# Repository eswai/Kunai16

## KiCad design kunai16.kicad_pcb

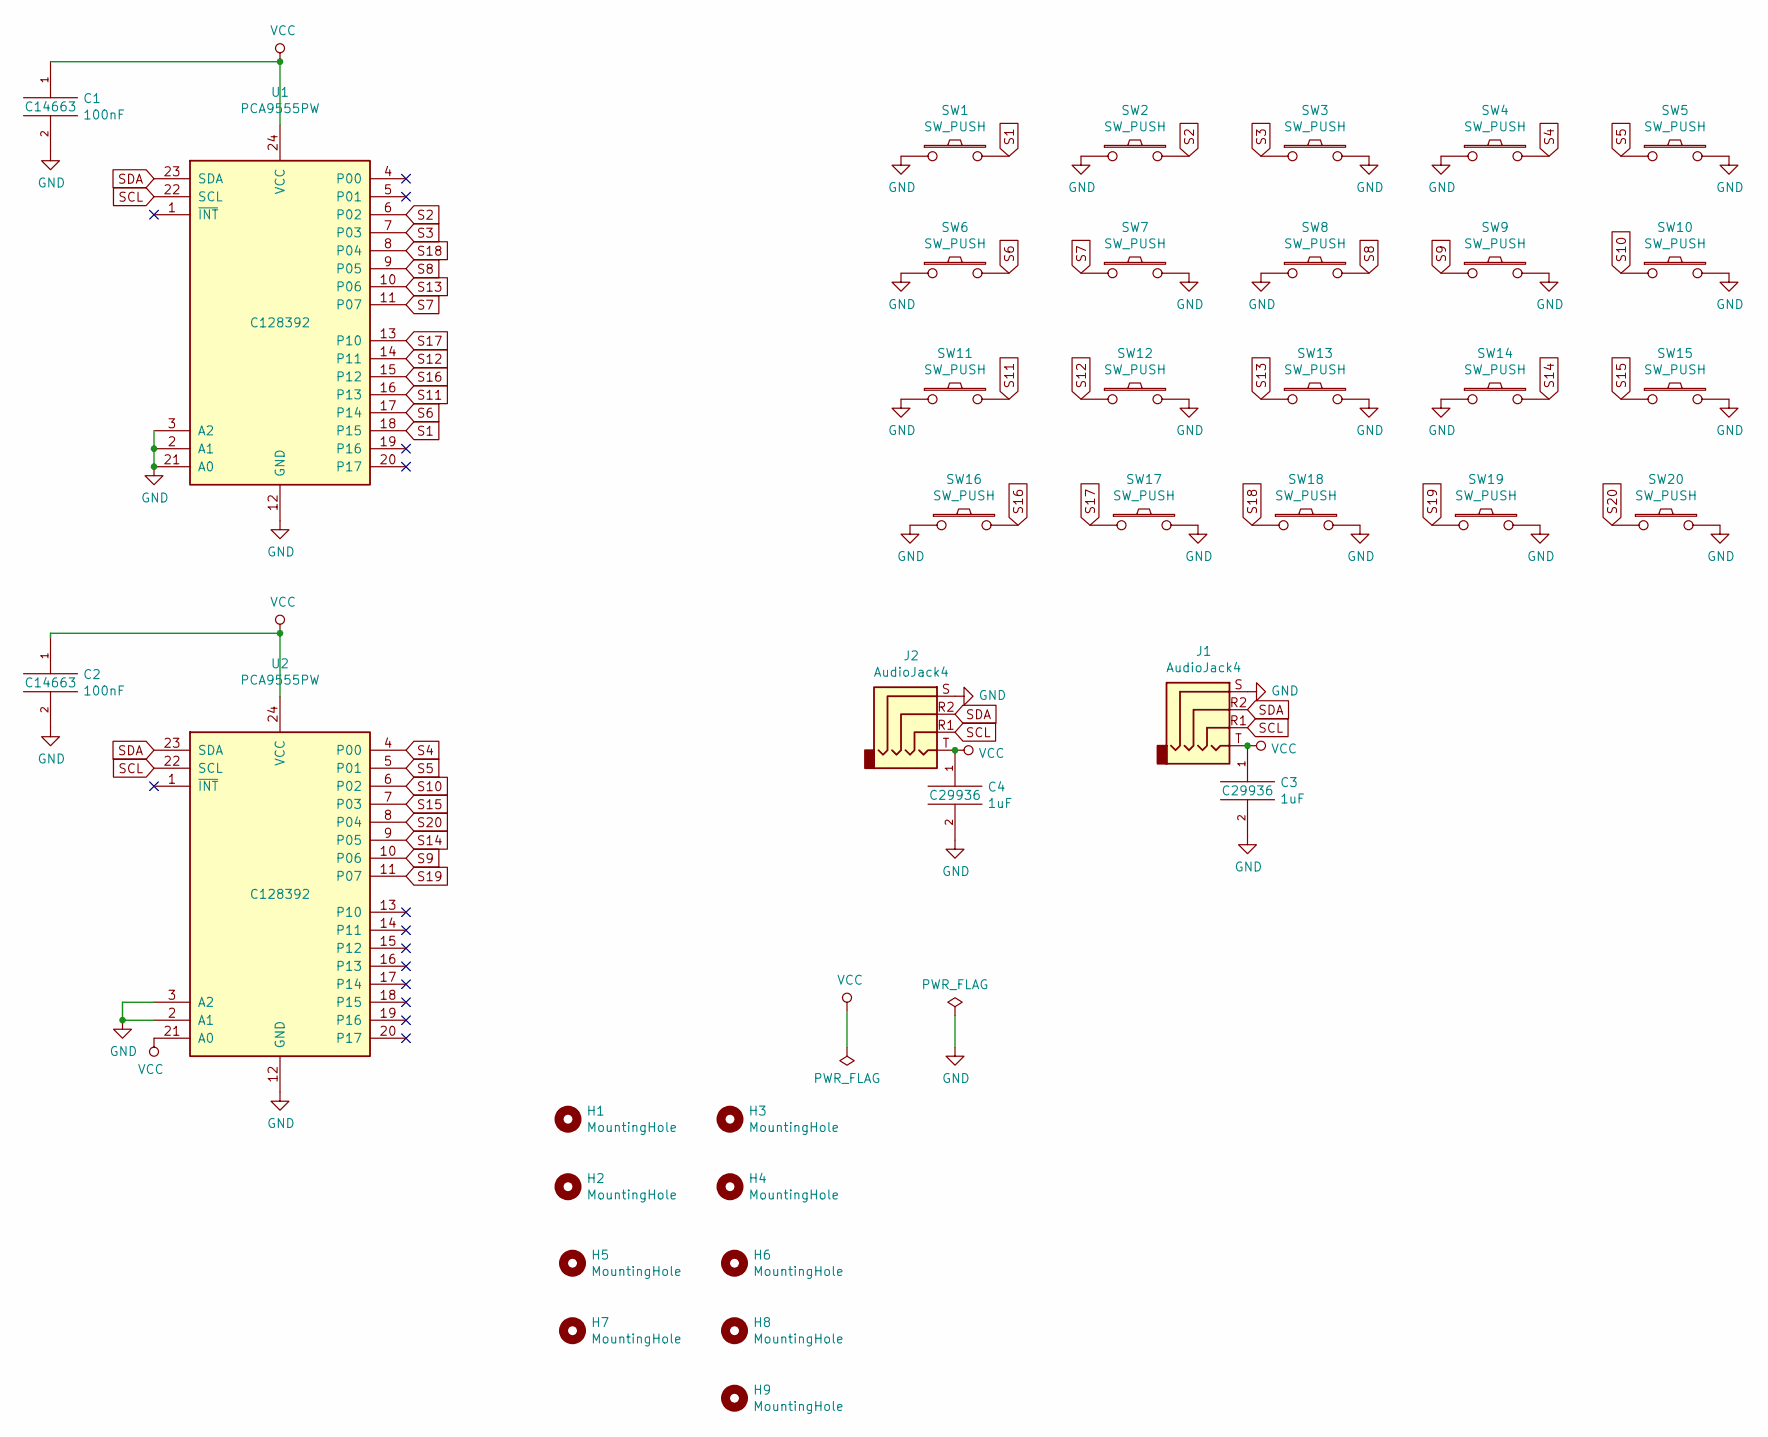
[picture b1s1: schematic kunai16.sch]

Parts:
C1, C2: 100nF; C_0603_1608Metric_Pad1.05x0.95mm_HandSolder; LCSC C14663
C3, C4: 1uF; C_0603_1608Metric_Pad1.05x0.95mm_HandSolder; LCSC C29936
H1, H2, H3, H4, H5, H6, H7, H8, H9: MountingHole; MountingHole_2.2mm_M2
J1, J2: AudioJack4; MJ-4PP-9_v3
SW1, SW2, SW3, SW4, SW5, SW6, SW7, SW8, SW9, SW10, SW11, SW12, SW13, SW14, SW15, SW16, SW17, SW18, SW19, SW20: SW_PUSH; CherryMX_Hotswap
U1, U2: PCA9555PW; TSSOP-24_4.4x7.8mm_P0.65mm; LCSC C128392

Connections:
GND: C1.2, C2.2, C3.2, C4.2, J1.S, J2.S, SW1.1, SW2.1, SW3.2, SW4.1, SW5.2, SW6.1, SW7.2, SW8.1, SW9.2, SW10.2, SW11.1, SW12.2, SW13.2, SW14.1, SW15.2, SW16.1, SW17.2, SW18.2, SW19.2, SW20.2, U1.2 (A1), U1.3 (A2), U1.12 (GND), U1.21 (A0), U2.2 (A1), U2.3 (A2), U2.12 (GND)
S1: SW1.2, U1.18 (P15)
S2: SW2.2, U1.6 (P02)
S3: SW3.1, U1.7 (P03)
S4: SW4.2, U2.4 (P00)
S5: SW5.1, U2.5 (P01)
S6: SW6.2, U1.17 (P14)
S7: SW7.1, U1.11 (P07)
S8: SW8.2, U1.9 (P05)
S9: SW9.1, U2.10 (P06)
S10: SW10.1, U2.6 (P02)
S11: SW11.2, U1.16 (P13)
S12: SW12.1, U1.14 (P11)
S13: SW13.1, U1.10 (P06)
S14: SW14.2, U2.9 (P05)
S15: SW15.1, U2.7 (P03)
S16: SW16.2, U1.15 (P12)
S17: SW17.1, U1.13 (P10)
S18: SW18.1, U1.8 (P04)
S19: SW19.1, U2.11 (P07)
S20: SW20.1, U2.8 (P04)
SCL: J1.R1, J2.R1, U1.22 (SCL), U2.22 (SCL)
SDA: J1.R2, J2.R2, U1.23 (SDA), U2.23 (SDA)
VCC: C1.1, C2.1, C3.1, C4.1, J1.T, J2.T, U1.24 (VCC), U2.21 (A0), U2.24 (VCC)

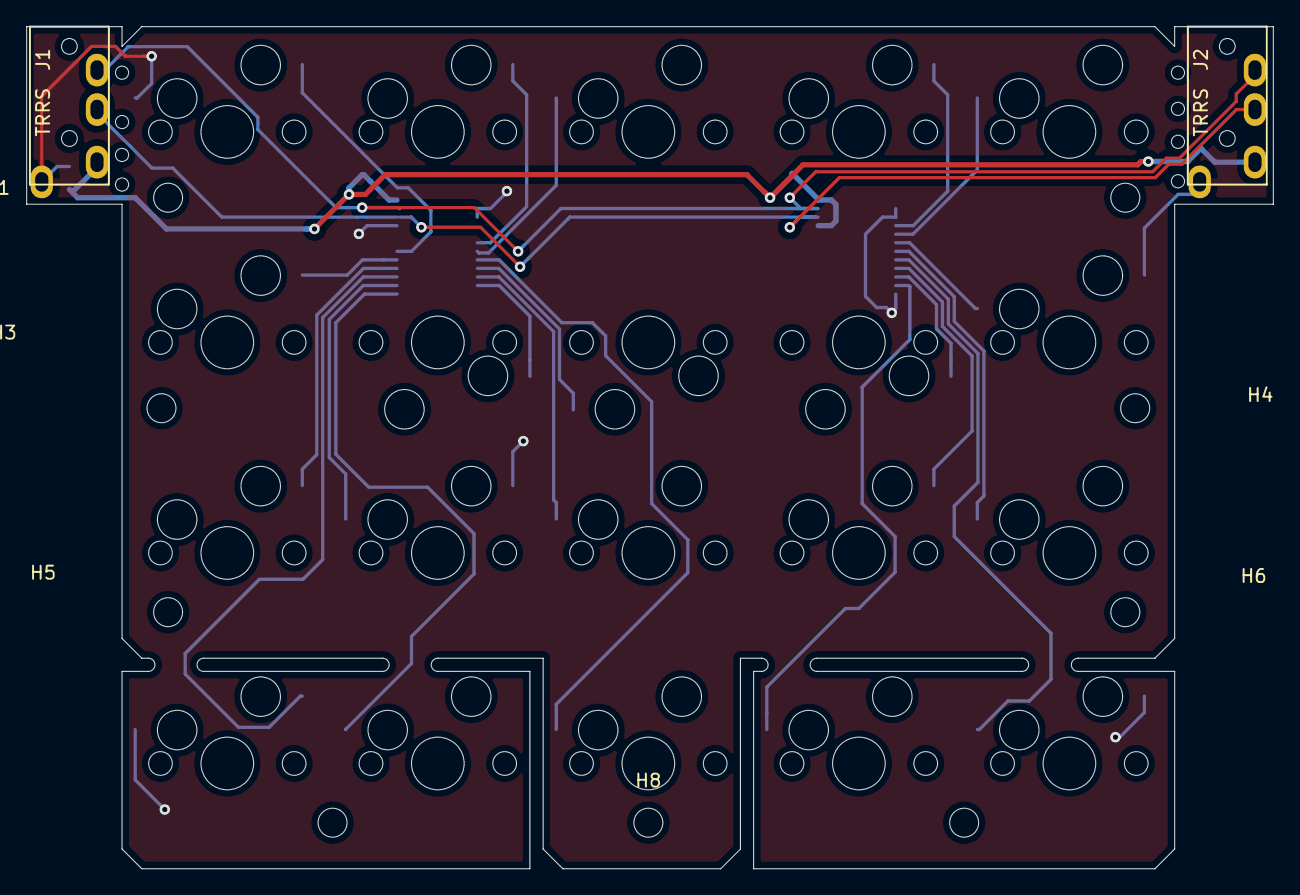
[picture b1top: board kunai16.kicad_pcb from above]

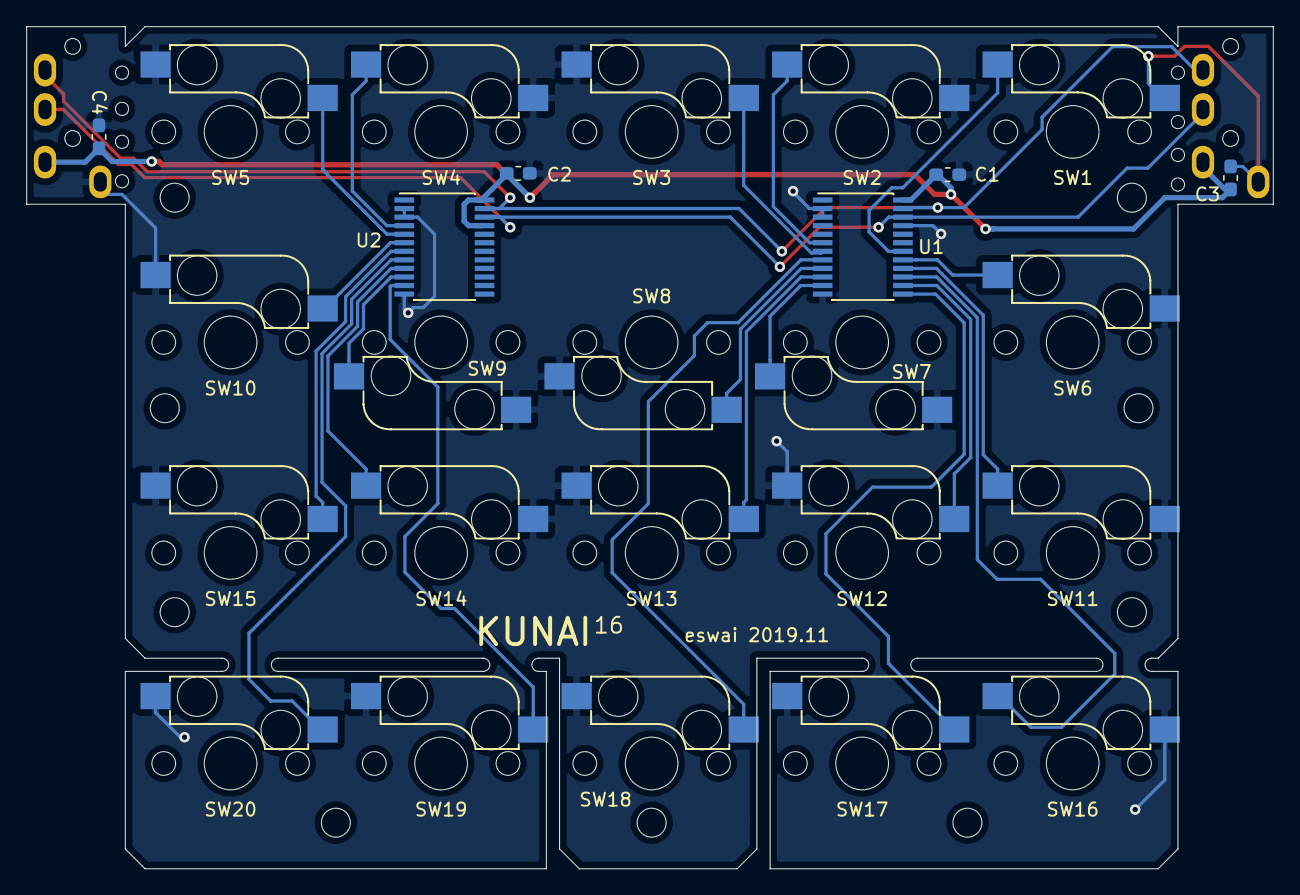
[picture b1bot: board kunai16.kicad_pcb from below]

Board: 2 copper layers, 94.8 x 64.0 mm, 45 parts (6 on the bottom side), 24 nets.

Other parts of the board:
Ref**: Val**; HOLE_copy
Ref**#2, Ref**#3, Ref**#4, Ref**#5, Ref**#6, Ref**#7, Ref**#8: Val**; HOLE_copy
